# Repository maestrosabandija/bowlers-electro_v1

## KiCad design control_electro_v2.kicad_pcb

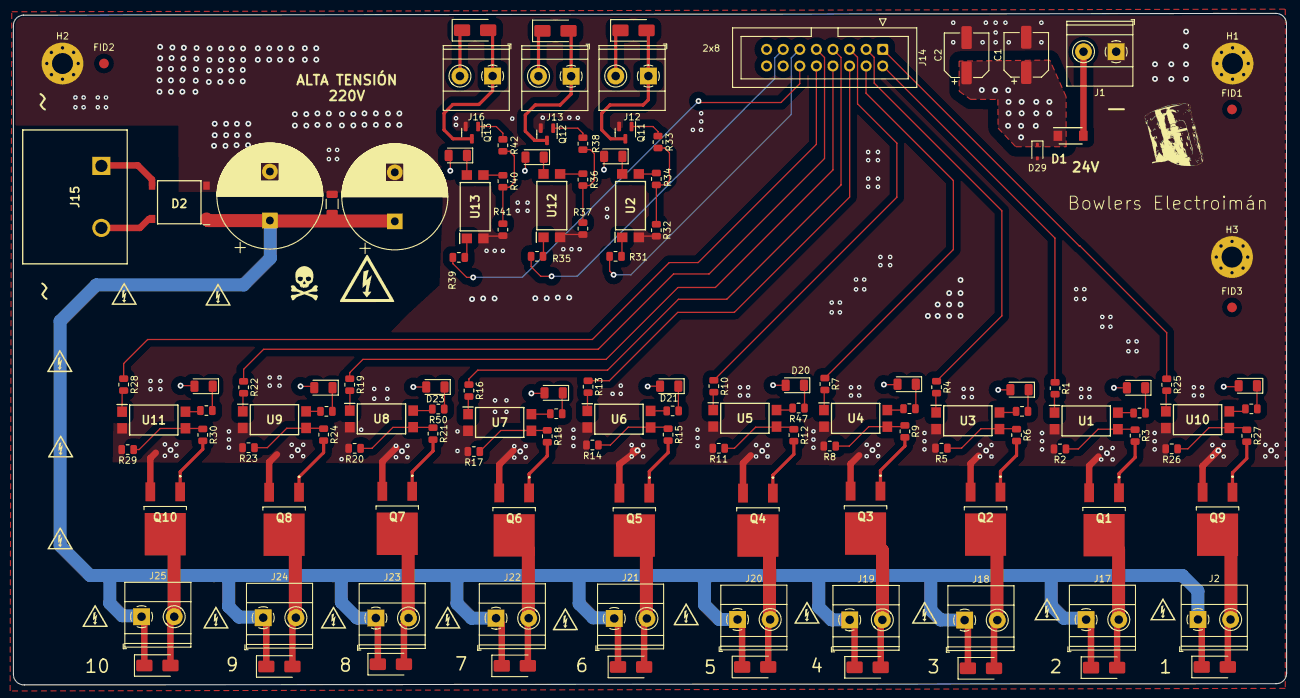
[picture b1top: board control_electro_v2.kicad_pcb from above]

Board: 4 copper layers, 195.0 x 102.8 mm, 134 parts (0 on the bottom side), 97 nets.

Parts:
C1, C2: 100u; CP_Elec_6.3x7.7
C3, C4: 33u; CP_Radial_D16.0mm_P7.50mm
D1: SM340AF; SODFL4625X120N
D2: D_Bridge_+-AA; SOTFL510P865X150-4N
D3, D4, D5, D6, D7, D8, D9, D10, D11, D12, D13, D14, D15: D_Flyback; D_SMA
D16, D17, D18, D19, D20, D21, D22, D23, D24, D25, D26, D27, D28: LED_Small; LED_1206_3216Metric
D29: 1N5819WS; D_SOD-323
FID1, FID2, FID3: Fiducial; Fiducial_1.5mm_Mask3mm
H1, H2, H3: MountHole; MountingHole_3.2mm_M3_Pad_Via
J1, J2, J12, J13, J16, J17, J18, J19, J20, J21, J22, J23, J24, J25: Screw_Terminal_01x02; TerminalBlock_Phoenix_MKDS-1,5-2_1x02_P5.00mm_Horizontal
J14: Conn_02x08_Odd_Even; IDC-Header_2x08_P2.54mm_Vertical
J15: HB9500M952P
Q1, Q2, Q3, Q4, Q5, Q6, Q7, Q8, Q9, Q10: STD6N95K5; STD13N60DM2
Q11, Q12, Q13: SI2308; SOT-23
R1, R4, R7, R10, R13, R16, R19, R22, R25, R28, R31, R35, R39: 1k; R_0805_2012Metric
R2, R5, R8, R11, R14, R17, R20, R23, R26, R29, R32, R34, R36, R37, R40, R41: 15k; R_0805_2012Metric
R3, R6, R9, R12, R15, R18, R21, R24, R27, R30, R33, R38, R42: 22; R_0805_2012Metric
R43, R44, R45, R46, R47, R48, R49, R50, R51, R52: 5k1; R_0805_2012Metric
R53: 1M; R_1206_3216Metric
U1, U2, U3, U4, U5, U6, U7, U8, U9, U10, U11, U12, U13: LTV-817S; SOP254P1030X390-4N

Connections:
+24V: C1.1, C2.1, D1.1 (K), D13.1 (K), D14.1 (K), D15.1 (K), D16.2 (A), D17.2 (A), D18.2 (A), D19.2 (A), D20.2 (A), D21.2 (A), D22.2 (A), D23.2 (A), D24.2 (A), D25.2 (A), D26.2 (A), D27.2 (A), D28.2 (A), D29.1 (K), J12.2, J13.2, J16.2
+VSW: D2.3, J15.1
-VSW: D2.4, J15.2
/Electroiman_220DC/Mosfet_Opto1/In_Gate: Q1.1 (G), R3.2
/Electroiman_220DC/Mosfet_Opto1/mos_drain: D4.2 (A), J17.2, Q1.2 (D)
/Electroiman_220DC/Mosfet_Opto2/In_Gate: Q2.1 (G), R6.2
/Electroiman_220DC/Mosfet_Opto2/mos_drain: D5.2 (A), J18.2, Q2.2 (D)
/Electroiman_220DC/Mosfet_Opto3/In_Gate: Q4.1 (G), R12.2
/Electroiman_220DC/Mosfet_Opto3/mos_drain: D7.2 (A), J20.2, Q4.2 (D)
/Electroiman_220DC/Mosfet_Opto4/In_Gate: Q10.1 (G), R30.2
/Electroiman_220DC/Mosfet_Opto4/mos_drain: D12.2 (A), J25.2, Q10.2 (D)
/Electroiman_220DC/Mosfet_Opto5/In_Gate: Q3.1 (G), R9.2
/Electroiman_220DC/Mosfet_Opto5/mos_drain: D6.2 (A), J19.2, Q3.2 (D)
/Electroiman_220DC/Mosfet_Opto6/In_Gate: Q8.1 (G), R24.2
/Electroiman_220DC/Mosfet_Opto6/mos_drain: D11.2 (A), J24.2, Q8.2 (D)
/Electroiman_220DC/Mosfet_Opto7/In_Gate: Q7.1 (G), R21.2
/Electroiman_220DC/Mosfet_Opto7/mos_drain: D10.2 (A), J23.2, Q7.2 (D)
/Electroiman_220DC/Mosfet_Opto8/In_Gate: Q6.1 (G), R18.2
/Electroiman_220DC/Mosfet_Opto8/mos_drain: D9.2 (A), J22.2, Q6.2 (D)
/Electroiman_220DC/Mosfet_Opto9/In_Gate: Q5.1 (G), R15.2
/Electroiman_220DC/Mosfet_Opto9/mos_drain: D8.2 (A), J21.2, Q5.2 (D)
/Electroiman_220DC/Mosfet_Opto/In_Gate: Q9.1 (G), R27.2
/Electroiman_220DC/Mosfet_Opto/mos_drain: D3.2 (A), J2.2, Q9.2 (D)
/IN1_1: J14.1, R25.1
/IN1_2: J14.11, R31.1
/IN2_1: J14.2, R1.1
/IN2_2: J14.12, R39.1
/IN3_1: J14.3, R4.1
/IN3_2: J14.13, R35.1
/IN4_1: J14.4, R7.1
/IN5_1: J14.5, R10.1
/IN6_1: J14.6, R13.1
/IN7_1: J14.7, R16.1
/IN8_1: J14.8, R19.1
/IN9_1: J14.9, R22.1
/IN10_1: J14.10, R28.1
GND: C1.2, C2.2, C3.2, C4.2, D2.2 (-), D29.2 (A), H1.1, H2.1, H3.1, J1.1, Q1.3 (S), Q2.3 (S), Q3.3 (S), Q4.3 (S), Q5.3 (S), Q6.3 (S), Q7.3 (S), Q8.3 (S), Q9.3 (S), Q10.3 (S), Q11.2 (S), Q12.2 (S), Q13.2 (S), R2.2, R5.2, R8.2, R11.2, R14.2, R17.2, R20.2, R23.2, R26.2, R29.2, R32.2, R37.2, R41.2, R53.2, U1.2, U2.2, U3.2, U4.2, U5.2, U6.2, U7.2, U8.2, U9.2, U10.2, U11.2, U12.2, U13.2
unnamed: D1.2 (A), J1.2
unnamed: D13.2 (A), J12.1, Q11.3 (D)
unnamed: D14.2 (A), J13.1, Q12.3 (D)
unnamed: D15.2 (A), J16.1, Q13.3 (D)
unnamed: D16.1 (K), R43.1
unnamed: D17.1 (K), R44.1
unnamed: D18.1 (K), R45.1
unnamed: D19.1 (K), R46.1
unnamed: D20.1 (K), R47.1
unnamed: D21.1 (K), R48.1
unnamed: D22.1 (K), R49.1
unnamed: D23.1 (K), R50.1
unnamed: D24.1 (K), R51.1
unnamed: D25.1 (K), R52.1
unnamed: D26.1 (K), U2.4
unnamed: D27.1 (K), U12.4
unnamed: D28.1 (K), U13.4
unnamed: Q11.1 (G), R33.2
unnamed: Q12.1 (G), R38.2
unnamed: Q13.1 (G), R42.2
unnamed: R1.2, U1.1
unnamed: R2.1, R3.1, U1.3
unnamed: R4.2, U3.1
unnamed: R5.1, R6.1, U3.3
unnamed: R7.2, U4.1
unnamed: R8.1, R9.1, U4.3
unnamed: R10.2, U5.1
unnamed: R11.1, R12.1, U5.3
unnamed: R13.2, U6.1
unnamed: R14.1, R15.1, U6.3
unnamed: R16.2, U7.1
unnamed: R17.1, R18.1, U7.3
unnamed: R19.2, U8.1
unnamed: R20.1, R21.1, U8.3
unnamed: R22.2, U9.1
unnamed: R23.1, R24.1, U9.3
unnamed: R25.2, U10.1
unnamed: R26.1, R27.1, U10.3
unnamed: R28.2, U11.1
unnamed: R29.1, R30.1, U11.3
unnamed: R31.2, U2.1
unnamed: R32.1, R33.1, R34.1
unnamed: R34.2, U2.3
unnamed: R35.2, U12.1
unnamed: R36.1, R37.1, R38.1
unnamed: R36.2, U12.3
unnamed: R39.2, U13.1
unnamed: R40.1, R41.1, R42.1
unnamed: R40.2, U13.3
unnamed: R43.2, U10.4
unnamed: R44.2, U1.4
unnamed: R45.2, U3.4
unnamed: R46.2, U4.4
unnamed: R47.2, U5.4
unnamed: R48.2, U6.4
unnamed: R49.2, U7.4
unnamed: R50.2, U8.4
unnamed: R51.2, U9.4
unnamed: R52.2, U11.4
VDD: C3.1, C4.1, D2.1 (+), D3.1 (K), D4.1 (K), D5.1 (K), D6.1 (K), D7.1 (K), D8.1 (K), D9.1 (K), D10.1 (K), D11.1 (K), D12.1 (K), J2.1, J17.1, J18.1, J19.1, J20.1, J21.1, J22.1, J23.1, J24.1, J25.1, R53.1

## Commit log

2025-05-07 electro v1
